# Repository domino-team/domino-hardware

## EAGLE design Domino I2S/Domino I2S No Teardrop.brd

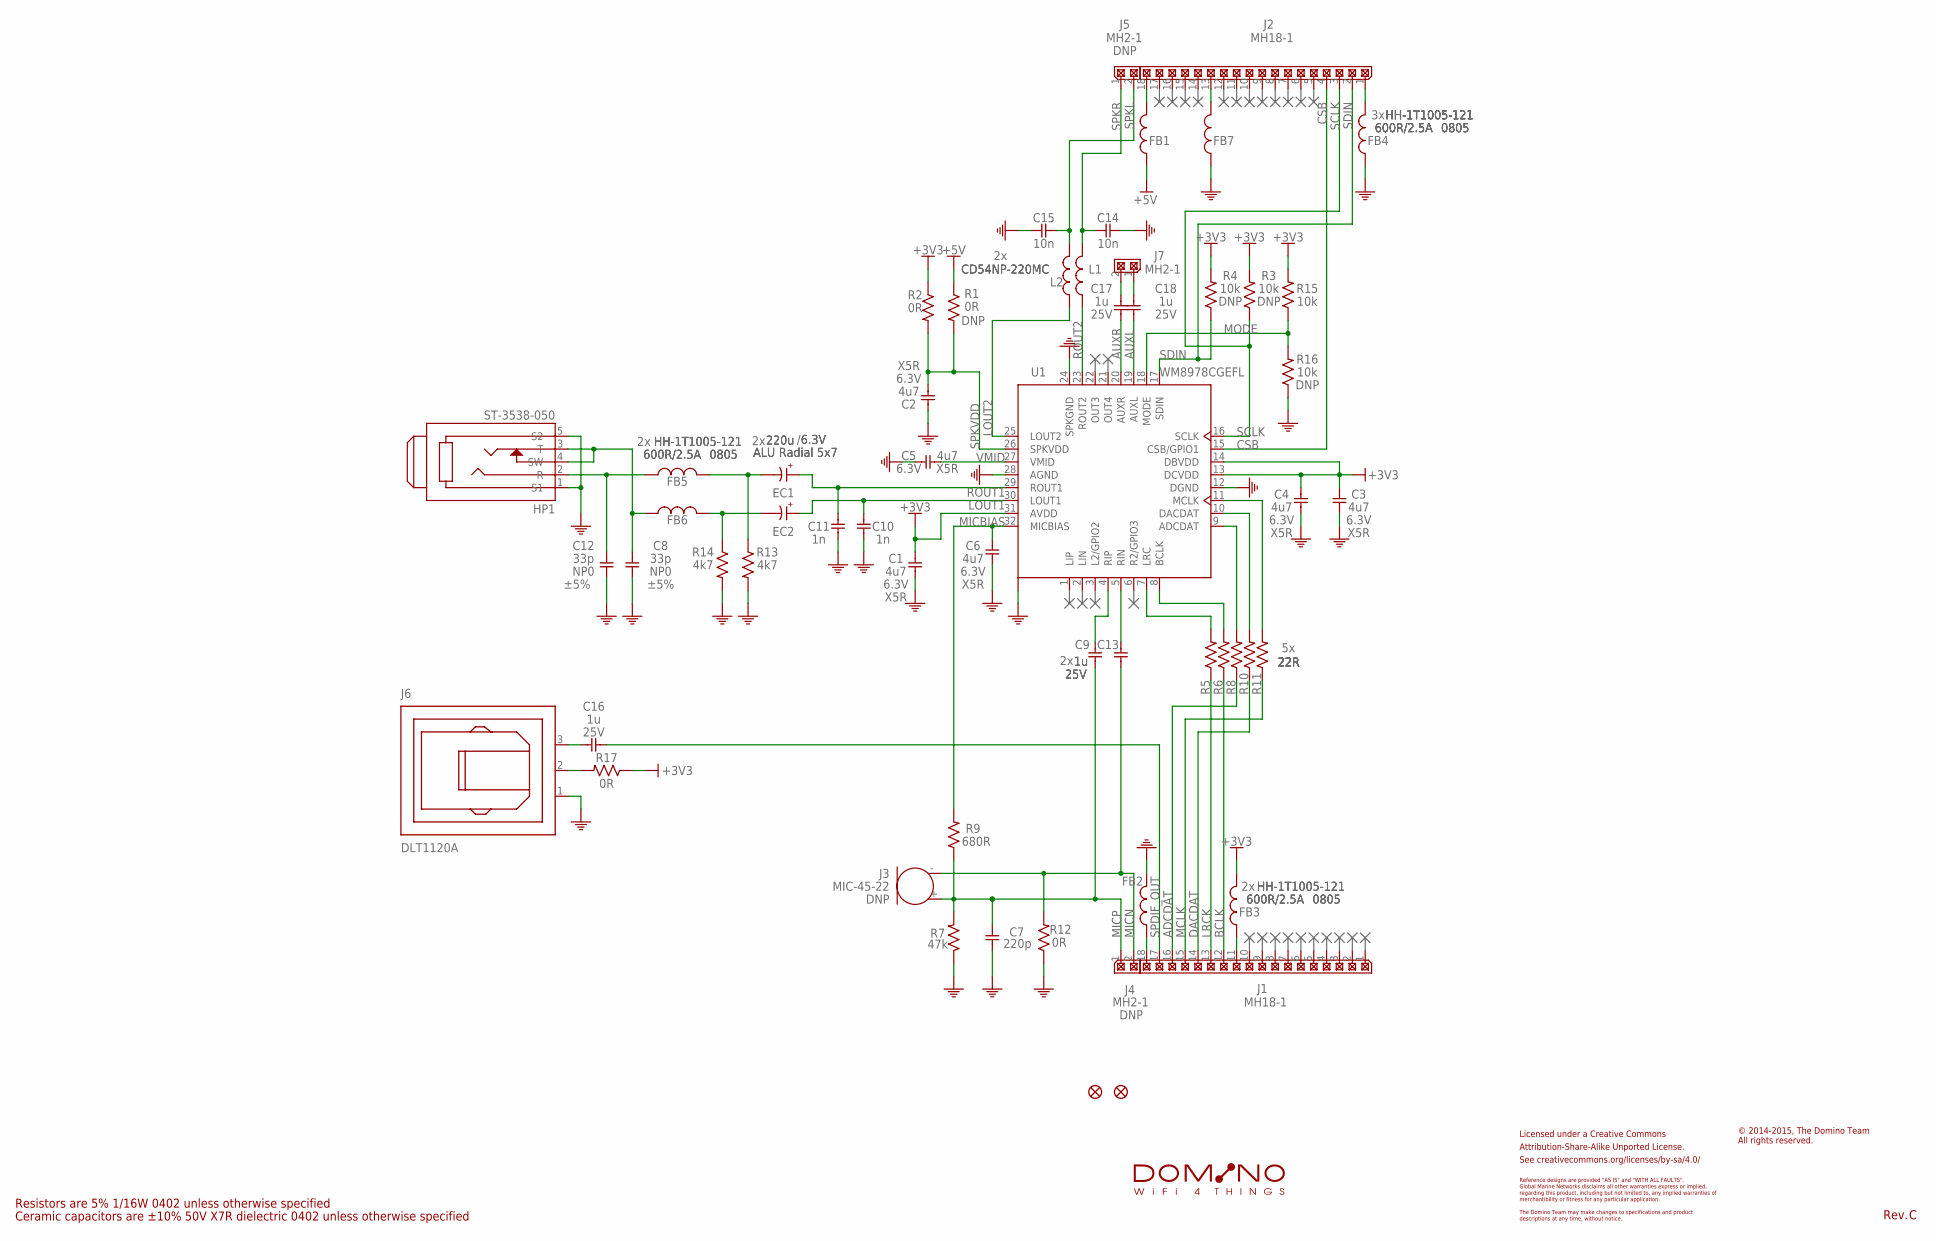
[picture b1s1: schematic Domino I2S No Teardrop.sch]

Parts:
C1, C2, C3, C4, C5, C6: 4u7; C0402; PARTNO C0402_4u7_X5R_10%_CER_6V3
C7: 220p; C0402; PARTNO C0402_220p_X7R_10%_CER_50V
C8, C12: 33p; C0402; PARTNO C0402_33p_NP0_5%_CER_50V
C9, C13, C16, C17, C18: 1u; C0402; PARTNO C0402_1u_X7R_10%_CER_25V
C10, C11: 1n; C0402; PARTNO C0402_1n_X7R_10%_CER_50V
C14, C15: 10n; C0402; PARTNO C0402_10n_X7R_10%_CER_50V
CC-BY-SA101: CC-BY-SA_LOGO
EC1, EC2: 220u; E2-5; PARTNO C2-5x7_220u_ALU_20%_RAD_6V3
F1, F2: FIDUCIAL
FB1, FB2, FB3, FB4, FB5, FB6, FB7: HH-1T1005-121; FB0805; PARTNO HH-1T2012-601
HP1: ST-3538-050; PARTNO ST-3538-050
J1, J2: MH18-1; MH18-1-0.1; PARTNO MH18-1-0.1
J3: MIC-45-22; PARTNO MIC-45-22
J4, J5, J7: MH2-1; MH2-1-0.1; PARTNO MH2-1-0.1
J6: DLT1120A; PARTNO DLT1120A
L1, L2: CD54NP-220MC; CD54; PARTNO CD54NP-220MC
R1, R2, R12, R17: 0R; R0402; PARTNO R0402_0R_5%_62.5mW
R3, R4, R15, R16: 10k; R0402; PARTNO R0402_10k_5%_62.5mW
R5, R6, R8, R10, R11: 22R; R0402; PARTNO R0402_22R_5%_62.5mW
R7: 47k; R0402; PARTNO R0402_47k_5%_62.5mW
R9: 680R; R0402; PARTNO R0402_680R_5%_62.5mW
R13, R14: 4k7; R0402; PARTNO R0402_4k7_5%_62.5mW
S101: DOMINO_LOGO
U1: WM8978CGEFL; QFN-32_EP_5X5; PARTNO WM8978CGEFL

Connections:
+3V3: C1.1, C3.1, C4.1, FB3.2, R2.1, R3.2, R4.2, R15.2, R17.1, U1.13 (DCVDD), U1.14 (DBVDD), U1.31 (AVDD)
+5V: FB1.1, R1.1
ADCDAT: J1.16, R8.1
AUXL: C18.2, U1.19 (AUXL)
AUXR: C17.2, U1.20 (AUXR)
BCLK: J1.12, R6.1
CSB: J2.4, U1.15 (CSB/GPIO1)
DACDAT: J1.14, R10.1
GND: C1.2, C2.1, C3.2, C4.2, C5.1, C6.2, C7.2, C8.1, C10.2, C11.2, C12.1, C14.2, C15.2, FB2.2, FB4.1, FB7.1, HP1.1 (S1), HP1.5 (S2), J6.1 (GND), R7.1, R12.1, R13.2, R14.2, R16.1, U1.12 (DGND), U1.24 (SPKGND), U1.28 (AGND), U1.PAD
LOUT1: C10.1, EC2.1 (+), U1.30 (LOUT1)
LOUT2: L2.1, U1.25 (LOUT2)
LRCK: J1.13, R5.1
MCLK: J1.15, R11.1
MICBIAS: C6.1, R9.2, U1.32 (MICBIAS)
MICN: C13.2, J3.-, J4.2, R12.2
MICP: C7.1, C9.2, J3.+, J4.1, R7.2, R9.1
MODE: R15.1, R16.2, U1.18 (MODE)
unnamed: R5.2, U1.7 (LRC)
unnamed: R6.2, U1.8 (BCLK)
unnamed: R8.2, U1.9 (ADCDAT)
unnamed: R10.2, U1.10 (DACDAT)
unnamed: R11.2, U1.11 (MCLK)
unnamed: C9.1, U1.4 (RIP)
unnamed: C13.1, U1.5 (RIN)
unnamed: C16.1, J6.3 (VIN)
unnamed: J6.2 (VCC), R17.2
unnamed: FB2.1, J1.18
unnamed: FB1.2, J2.18
unnamed: EC1.2 (-), FB5.2, R13.1
unnamed: EC2.2 (-), FB6.2, R14.1
unnamed: FB3.1, J1.11
unnamed: FB7.2, J2.13
unnamed: C8.2, FB6.1, HP1.3 (T), HP1.4 (SW)
unnamed: C12.2, FB5.1, HP1.2 (R)
unnamed: FB4.2, J2.1
unnamed: C17.1, J7.2
unnamed: C18.1, J7.1
ROUT1: C11.1, EC1.1 (+), U1.29 (ROUT1)
ROUT2: L1.1, U1.23 (ROUT2)
SCLK: J2.3, R3.1, U1.16 (SCLK)
SDIN: J2.2, R4.1, U1.17 (SDIN)
SPDIF_OUT: C16.2, J1.17
SPKL: C15.1, J5.2, L2.2
SPKR: C14.1, J5.1, L1.2
SPKVDD: C2.2, R1.2, R2.2, U1.26 (SPKVDD)
VMID: C5.2, U1.27 (VMID)

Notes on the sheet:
Ceramic capacitors are ±10% 50V X7R dielectric 0402 unless otherwise specified
Resistors are 5% 1/16W 0402 unless otherwise specified
Licensed under a Creative Commons
Attribution-Share-Alike Unported License.
See creativecommons.org/licenses/by-sa/4.0/
Reference designs are provided "AS IS" and "WITH ALL FAULTS".
regarding this product, including but not limited to, any implied warranties of
The Domino Team may make changes to specifications and product
Global Marine Networks disclaims all other warranties express or implied,
merchantibility or fitness for any particular application.
descriptions at any time, without notice.
© 2014-2015, The Domino Team All rights reserved.
Rev.

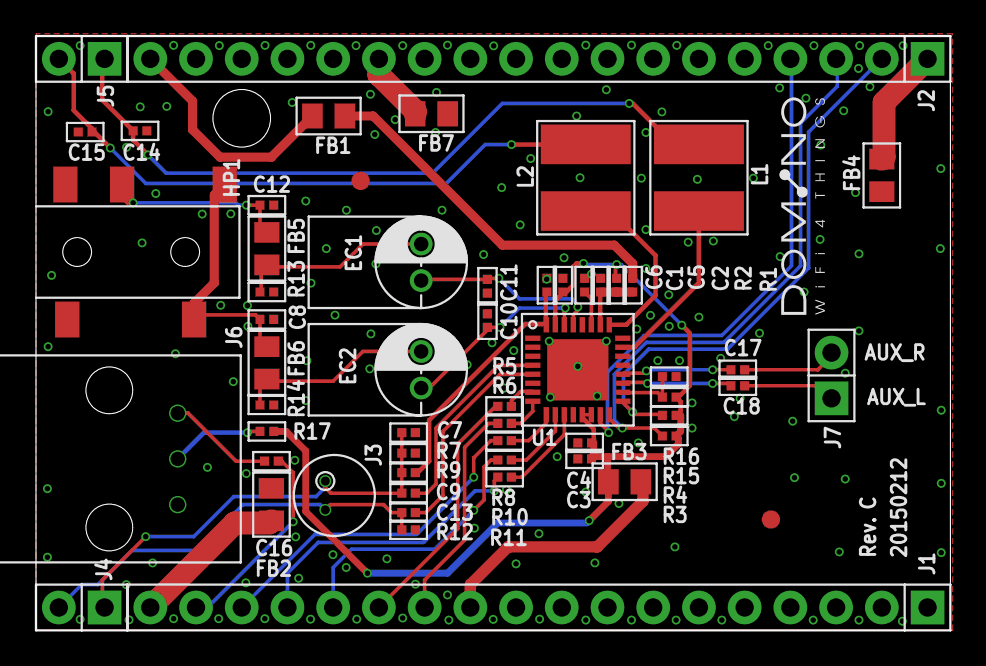
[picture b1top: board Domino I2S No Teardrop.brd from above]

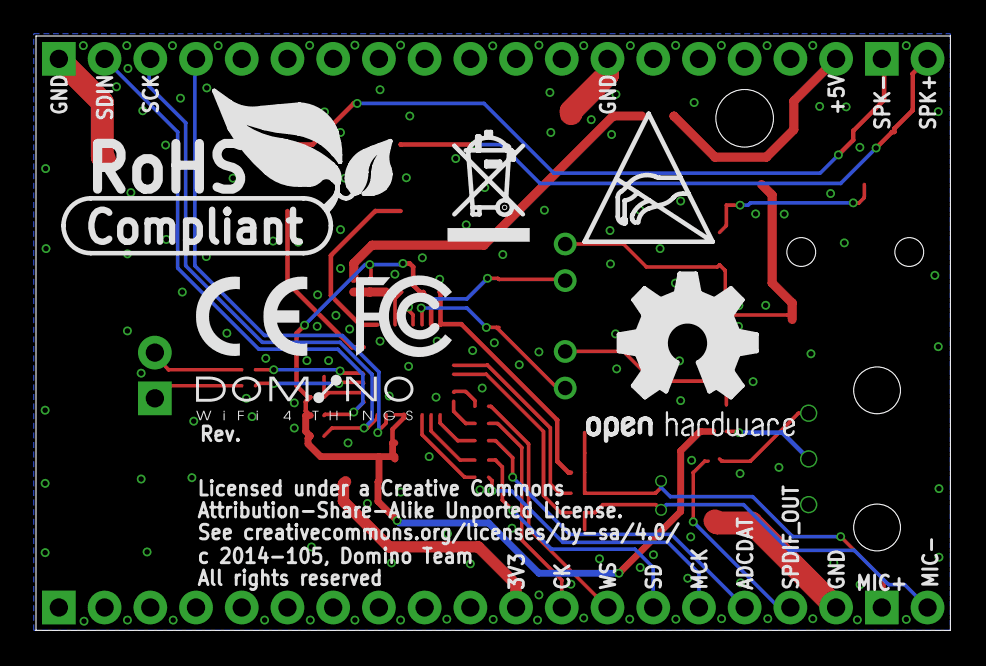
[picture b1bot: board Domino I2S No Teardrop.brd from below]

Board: 2 copper layers, 50.8 x 33.0 mm, 69 parts (7 on the bottom side), 46 nets.

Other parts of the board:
DRILEGEND: DRILEGEND
U$3: A5L-LOC
U$12, U$14: DOMINO_LOGO_SMALL
U$13: RECYCLE_BIN_LOGO
U$15: ESD_LOGO
U$16: OPEN_HARDWARE_LOGO
U$20: CE_LOGO_SMALL
U$21: FCC_LOGO_SMALL
U$22: ROHS_LOGO

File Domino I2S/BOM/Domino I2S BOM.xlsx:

Item | Qty | Value | Manufacturer | Device | Package | Reference | Description | Remarks
1 | 6 | 4u7 | ANY | C0402_4u7_X5R_10%_CER_6V3 | C0402 | C1, C2, C3, C4, C5, C6 | CAP CER 4.7UF 6.3V 10% X5R 0402
2 | 2 | 1n | ANY | C0402_1n_X7R_10%_CER_50V | C0402 | C10, C11 | CAP CER 1NF 50V 10% X7R 0402
3 | 2 | 10n | ANY | C0402_10n_X7R_10%_CER_50V | C0402 | C14, C15 | CAP CER 10000PF 50V 10% X7R 0402
4 | 1 | 220p | ANY | C0402_220p_X7R_10%_CER_50V | C0402 | C7 | CAP CER 0.22UF 50V 10% X7R 0402
5 | 2 | 33p | ANY | C0402_33p_NP0_5%_CER_50V | C0402 | C8, C12 | CAP CER 33PF 50V 5% NP0 0402
6 | 5 | 1u | ANY | C0402_1u_X7R_10%_CER_25V | C0402 | C9, C13, C16, C17, C18 | CAP CER 1UF 25V 10% X7R 0402
7 | 2 | 220u | ANY | C2-5x7_220u_ALU_20%_RAD_6V3 | E2-5 | EC1, EC2 | CAP ALUM 220UF 6.3V 20% RADIAL
8 | 7 | HH-1T1005-121 | CERATECH | HH-1T2012-601 | FB0805 | FB1, FB2, FB3, FB4, FB5, FB6, FB7 | FERRITE CHIP 600 OHM 2500MA 0805
9 | 1 | ST-3538-050 | SZJUSTWELL ELECTRONICS | ST-3538-050 | ST-3538-050 | HP1 | CONN AUDIO JACK 3.5MM STEREO SMD
10 | 2 | MH18-1 | ANY | MH18-1-0.1 | MH18-1-0.1 | J1, J2 | CONN HEADER VERT .100 1ROW 18POS 8.08 HEAD 3.05 TAIL 15AU
11 | 0 | MIC-45-22 | ANY | MIC-45-22 | MIC-45-22 | J3(DNP) | MIC COND ANALOG OMNI
12 | 1 | MH2-1 | ANY | MH2-1-0.1 | MH2-1-0.1 | J4(DNP), J5(DNP), J7 | CONN HEADER VERT .100 1ROW 2POS 8.08 HEAD 3.05 TAIL 15AU
13 | 1 | DLT1120A | AIXIN LTD | DLT1120A | DLT1120A | J6 | TRANSMITTER FIBER OPTIC 16MBPS
14 | 2 | CD54NP-220MC | SUMIDA INC | CD54NP-220MC | CD54 | L1, L2 | FIXED IND 220UH 1.11A 190 MOHM
15 | 3 | 0R | ANY | R0402_0R_5%_62.5mW | R0402 | R1(DNP), R2, R12, R17 | RES 0.0 OHM 1/16W JUMP 0402 SMD
16 | 2 | 4k7 | ANY | R0402_4k7_5%_62.5mW | R0402 | R13, R14 | RES 4.7K OHM 1/16W 5% 0402 SMD
17 | 1 | 10k | ANY | R0402_10k_5%_62.5mW | R0402 | R3(DNP), R4(DNP), R15, R16(DNP) | RES 10K OHM 1/16W 5% 0402 SMD
18 | 5 | 22R | ANY | R0402_22R_5%_62.5mW | R0402 | R5, R6, R8, R10, R11 | RES 22 OHM 1/16W 5% 0402 SMD
19 | 1 | 47k | ANY | R0402_47k_5%_62.5mW | R0402 | R7 | RES 47K OHM 1/16W 5% 0402 SMD
20 | 1 | 680R | ANY | R0402_680R_5%_62.5mW | R0402 | R9 | RES 680 OHM 1/16W 5% 0402 SMD
21 | 1 | WM8978CGEFL | CIRRUS LOGIC | WM8978CGEFL | QFN-32_EP_5X5 | U1 | IC CODEC STER SPEAKER DVR 32QF

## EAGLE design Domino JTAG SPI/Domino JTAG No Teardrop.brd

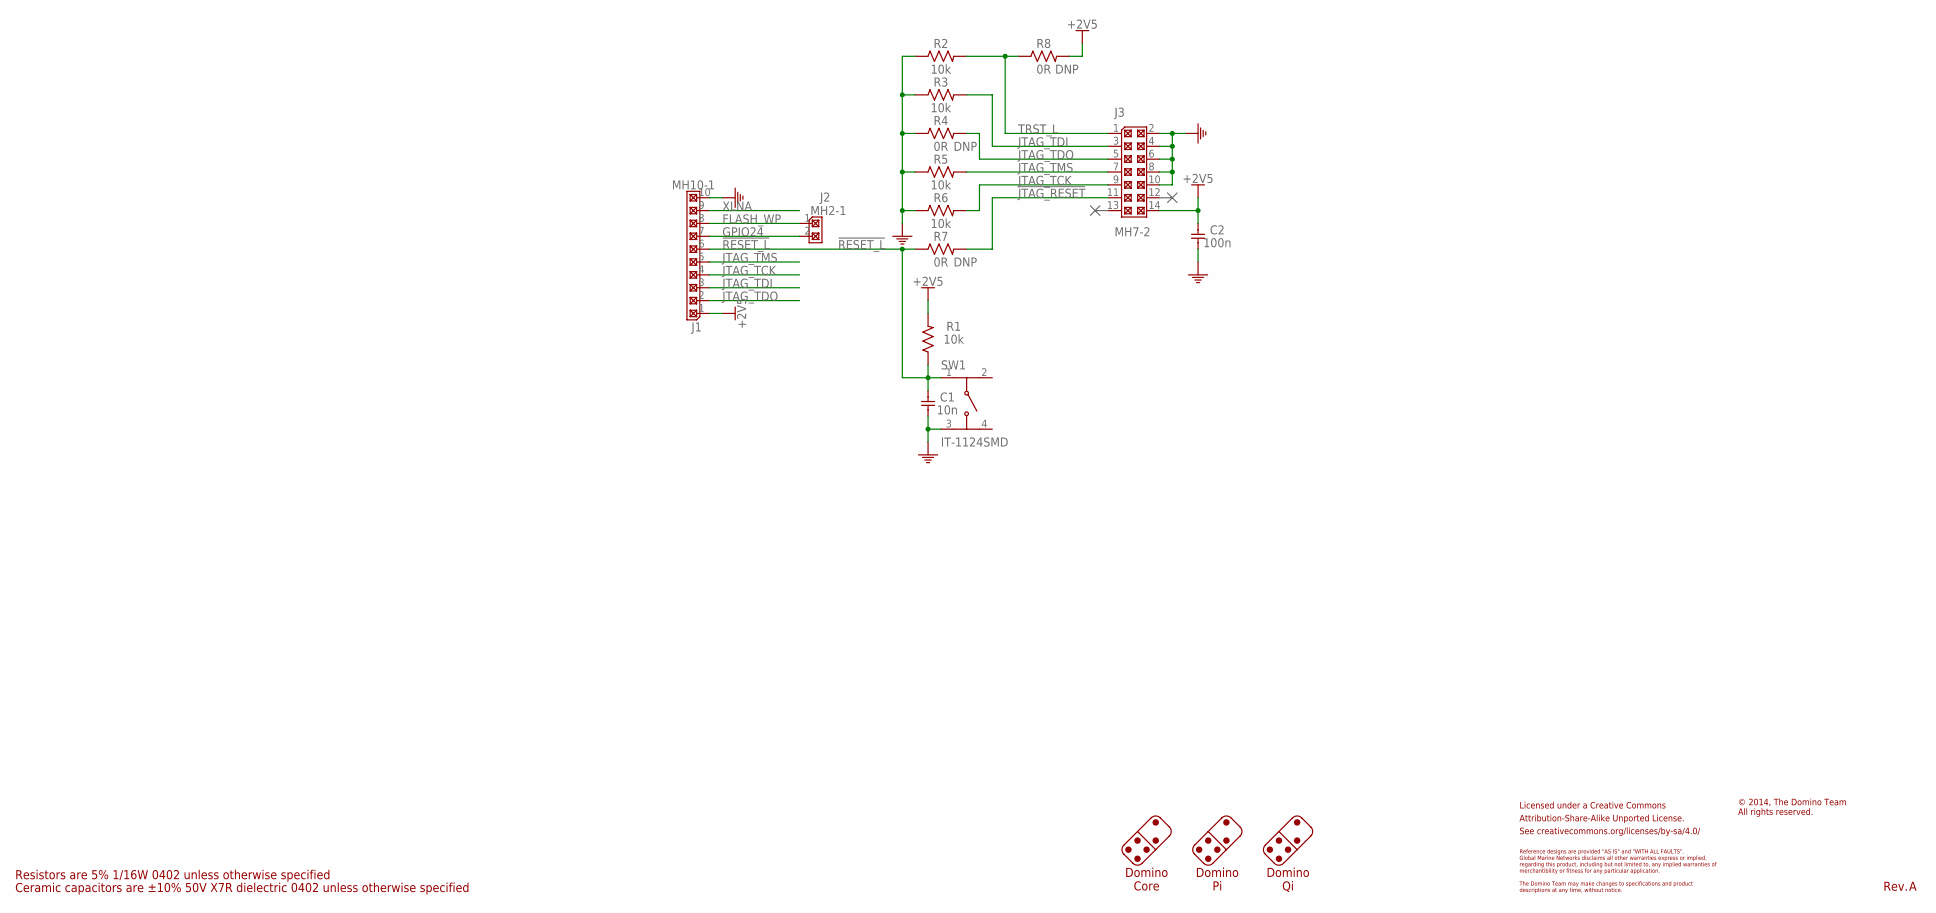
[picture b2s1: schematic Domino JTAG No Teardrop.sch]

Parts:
C1: 10n; C0402; PARTNO C0402_10n_X7R_10%_CER_50V
C2: 100n; C0402; PARTNO C0402_100n_X7R_10%_CER_50V
CC-BY-SA1: CC-BY-SA_LOGO
J1: MH10-1; MH10-1-0.1; PARTNO MH10-1-0.1
J2: MH2-1; MH2-1-0.1; PARTNO MH2-1-0.1
J3: MH7-2; MH7-2-0.1; PARTNO MH7-2-0.1
R1, R2, R3, R5, R6: 10k; R0402; PARTNO R0402_10k_5%_62.5mW
R4, R7, R8: 0R; R0603; PARTNO R0603_0R_5%_125mW
SW1: IT-1124SMD; PARTNO IT-1124SMD

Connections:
!JTAG_RESET: J3.11, R7.2
!RESET_L: C1.1, J1.6, R1.1, R7.1, SW1.1
+2V5: C2.1, J1.1, J3.14, R1.2, R8.2
FLASH_WP: J1.8, J2.1
GND: C1.2, C2.2, J1.10, J3.2, J3.4, J3.6, J3.8, J3.10, R2.1, R3.1, R4.1, R5.1, R6.1, SW1.3
GPIO24: J1.7, J2.2
JTAG_TCK: J1.4, J3.9, R6.2
JTAG_TDI: J1.3, J3.3, R3.2
JTAG_TDO: J1.2, J3.5, R4.2
JTAG_TMS: J1.5, J3.7, R5.2
TRST_L: J3.1, R2.2, R8.1
XLNA: J1.9

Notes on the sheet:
Ceramic capacitors are ±10% 50V X7R dielectric 0402 unless otherwise specified
Resistors are 5% 1/16W 0402 unless otherwise specified
Licensed under a Creative Commons
Attribution-Share-Alike Unported License.
See creativecommons.org/licenses/by-sa/4.0/
Reference designs are provided "AS IS" and "WITH ALL FAULTS".
regarding this product, including but not limited to, any implied warranties of
The Domino Team may make changes to specifications and product
Global Marine Networks disclaims all other warranties express or implied,
merchantibility or fitness for any particular application.
descriptions at any time, without notice.
Domino Core
Domino Pi
Domino Qi
© 2014, The Domino Team All rights reserved.
Rev.

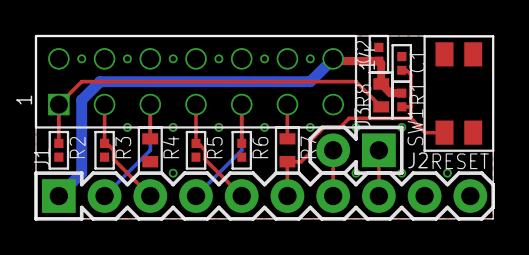
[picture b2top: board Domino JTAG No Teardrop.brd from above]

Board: 2 copper layers, 25.4 x 10.2 mm, 18 parts (1 on the bottom side), 11 nets.

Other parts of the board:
DRILEGEND: DRILEGEND
U$3: A5L-LOC
U$4: DOMINO_LOGO_SMALL

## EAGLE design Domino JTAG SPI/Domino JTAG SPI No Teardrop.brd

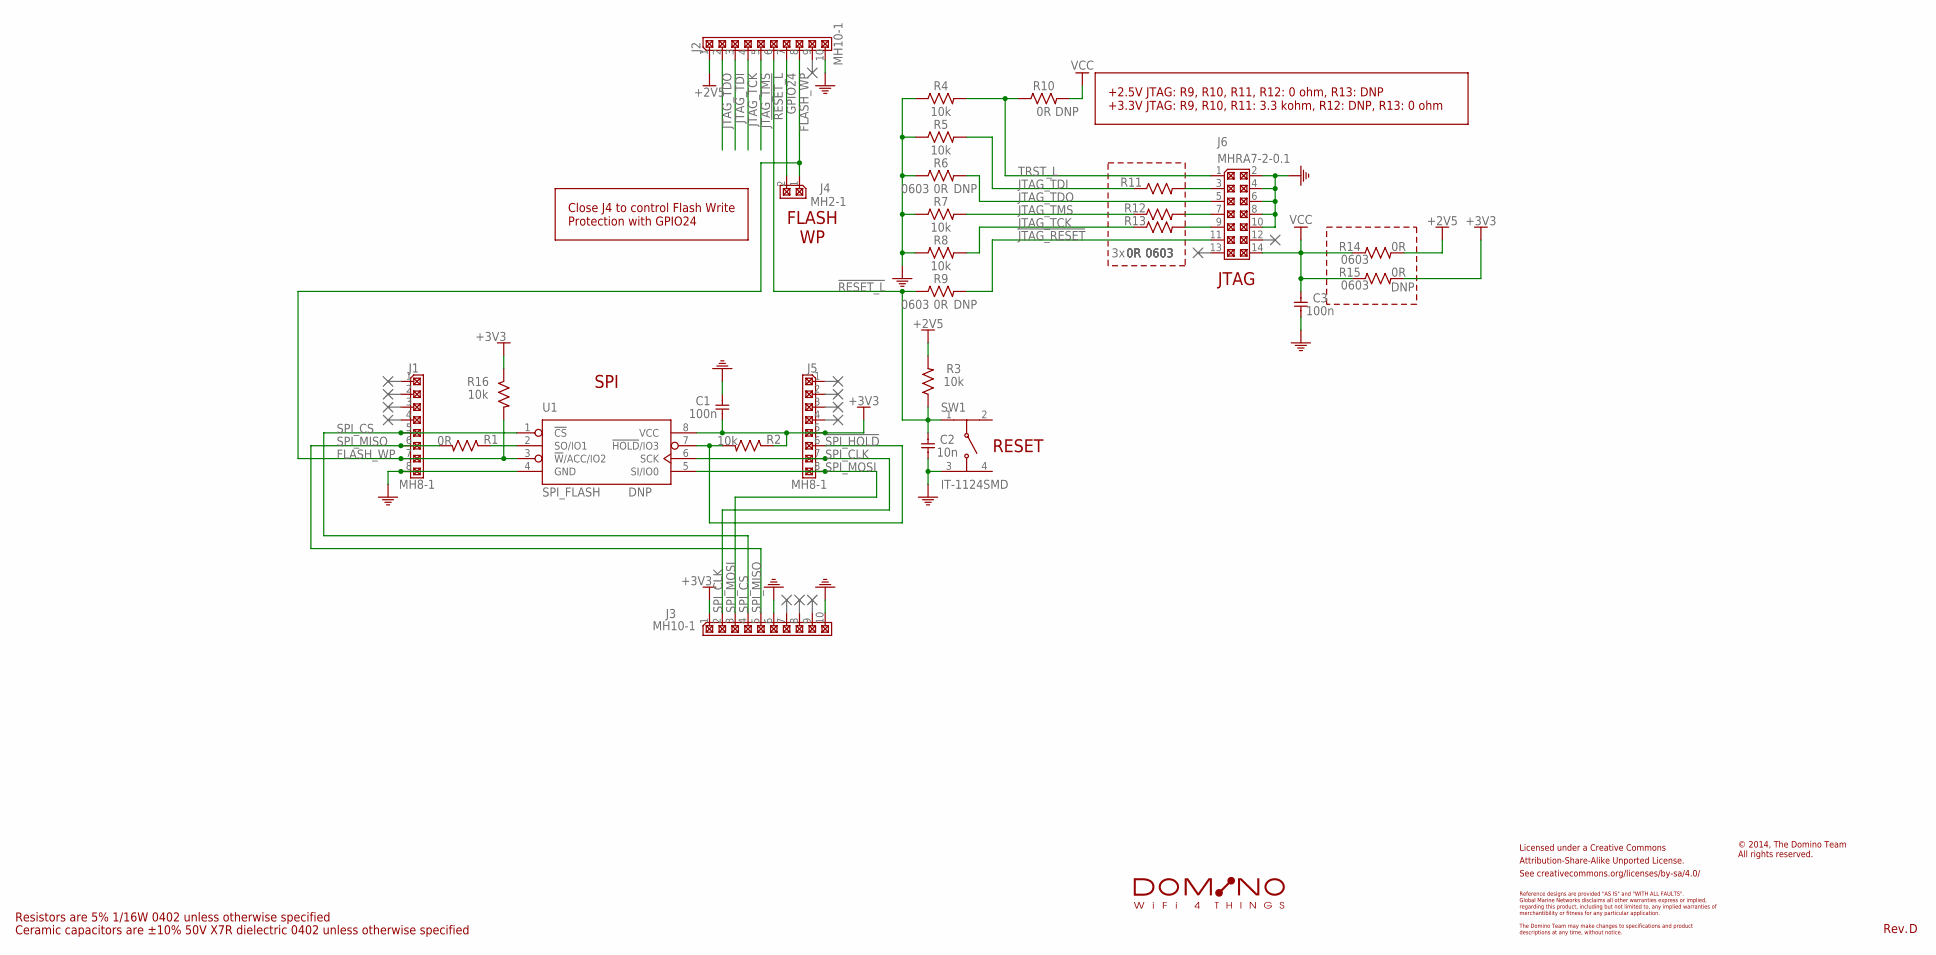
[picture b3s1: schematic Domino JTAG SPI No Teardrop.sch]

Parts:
C1, C3: 100n; C0402; PARTNO C0402_100n_X7R_10%_CER_50V
C2: 10n; C0402; PARTNO C0402_10n_X7R_10%_CER_50V
CC-BY-SA1: CC-BY-SA_LOGO
J1, J5: MH8-1; MH8-1-0.1; PARTNO MH8-1-0.1
J2, J3: MH10-1; MH10-1-0.1; PARTNO MH10-1-0.1
J4: MH2-1; MH2-1-0.1; PARTNO MH2-1-0.1
J6: MHRA7-2-0.1; PARTNO MHRA7-2-0.1
R1: 0R; R0402; PARTNO R0402_0R_5%_62.5mW
R2, R3, R4, R5, R7, R8, R16: 10k; R0402; PARTNO R0402_10k_5%_62.5mW
R6, R9, R10, R11, R12, R13, R14, R15: 0R; R0603; PARTNO R0603_0R_5%_125mW
SW1: IT-1124SMD; PARTNO IT-1124SMD
U1: SPI_FLASH; SOIC-8; PARTNO SPI_FLASH
U$2: DOMINO_LOGO

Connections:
!JTAG_RESET: J6.11, R9.2
!RESET_L: C2.1, J2.6, R3.1, R9.1, SW1.1
!SPI_HOLD: J5.6, R2.2, U1.7 (!HOLD!/IO3)
+2V5: J2.1, R3.2, R14.2
+3V3: C1.2, J3.1, J5.5, R2.1, R15.2, R16.1, U1.8 (VCC)
FLASH_WP: J1.7, J2.8, J4.1, R16.2, U1.3 (!W!/ACC/IO2)
GND: C1.1, C2.2, C3.2, J1.8, J2.10, J3.6, J3.10, J6.2, J6.4, J6.6, J6.8, J6.10, R4.1, R5.1, R6.1, R7.1, R8.1, SW1.3, U1.4 (GND)
GPIO24: J2.7, J4.2
JTAG_TCK: J2.4, R8.2, R13.1
JTAG_TDI: J2.3, R5.2, R11.1
JTAG_TDO: J2.2, J6.5, R6.2
JTAG_TMS: J2.5, R7.2, R12.1
unnamed: J6.7, R12.2
unnamed: J6.9, R13.2
unnamed: J6.3, R11.2
unnamed: R1.1, U1.2 (SO/IO1)
SPI_CLK: J3.2, J5.7, U1.6 (SCK)
SPI_CS: J1.5, J3.4, U1.1 (!CS)
SPI_MISO: J1.6, J3.5, R1.2
SPI_MOSI: J3.3, J5.8, U1.5 (SI/IO0)
TRST_L: J6.1, R4.2, R10.1
VCC: C3.1, J6.14, R10.2, R14.1, R15.1

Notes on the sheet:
Ceramic capacitors are ±10% 50V X7R dielectric 0402 unless otherwise specified
Resistors are 5% 1/16W 0402 unless otherwise specified
Licensed under a Creative Commons
Attribution-Share-Alike Unported License.
See creativecommons.org/licenses/by-sa/4.0/
Reference designs are provided "AS IS" and "WITH ALL FAULTS".
regarding this product, including but not limited to, any implied warranties of
The Domino Team may make changes to specifications and product
Global Marine Networks disclaims all other warranties express or implied,
merchantibility or fitness for any particular application.
descriptions at any time, without notice.
© 2014, The Domino Team All rights reserved.
Rev.
FLASH WP
SPI
JTAG
+2.5V JTAG: R9, R10, R11, R12: 0 ohm, R13: DNP +3.3V JTAG: R9, R10, R11: 3.3 kohm, R12: DNP, R13: 0 ohm
Close J4 to control Flash Write Protection with GPIO24
RESET

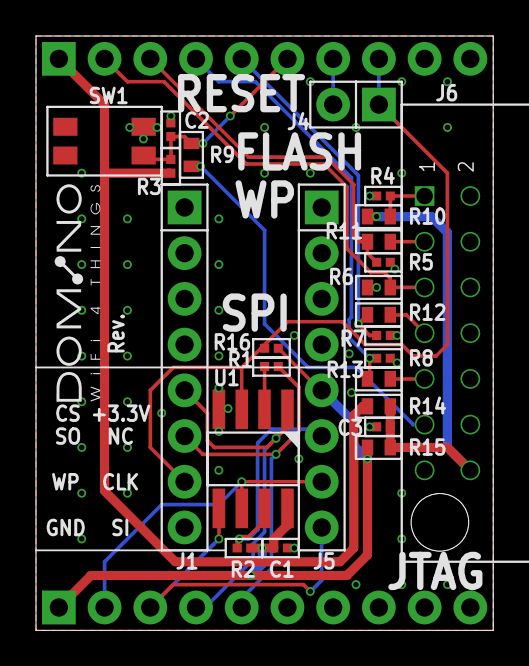
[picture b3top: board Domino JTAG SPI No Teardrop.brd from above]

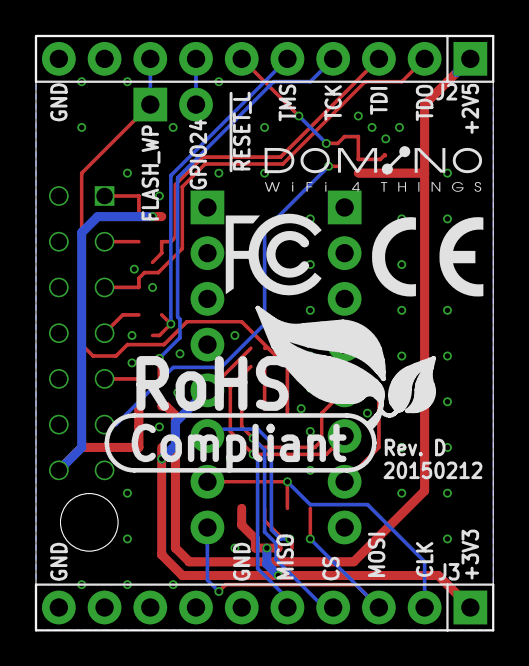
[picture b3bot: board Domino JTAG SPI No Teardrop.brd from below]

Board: 2 copper layers, 25.4 x 33.0 mm, 36 parts (6 on the bottom side), 22 nets.

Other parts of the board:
DRILEGEND: DRILEGEND
U$3: A5L-LOC
U$6: ROHS_LOGO
U$8: CE_LOGO_SMALL
U$10: FCC_LOGO_SMALL
U$11, U$12: DOMINO_LOGO_SMALL

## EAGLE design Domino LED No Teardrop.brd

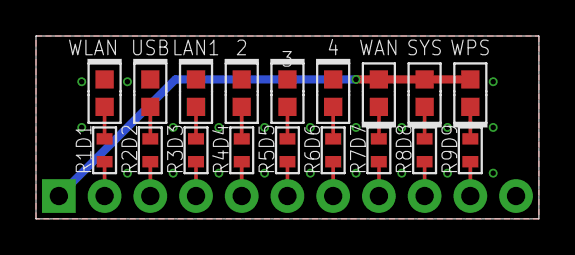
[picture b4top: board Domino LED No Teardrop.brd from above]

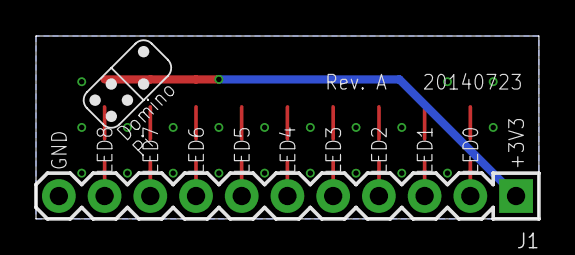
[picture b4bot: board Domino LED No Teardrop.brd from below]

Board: 2 copper layers, 27.9 x 10.2 mm, 23 parts (2 on the bottom side), 20 nets.

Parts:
CC-BY-SA1: CC-BY-SA_LOGO
D1: BLUE; LED0603
D2: WHITE; LED0603
D3, D4, D5, D6: GREEN; LED0603
D7: RED; LED0603
D8: ORANGE; LED0603
D9: YELLOW; LED0603
DRILEGEND: DRILEGEND
J1: MH11-1; MH11-1-0.1
R1, R2, R3, R4, R5, R6: 270R; R0603
R7, R8, R9: 330R; R0603
U$3: A5L-LOC
U$4: DOMINO_LOGO_SMALL

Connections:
+3V3: D7.2, D8.2, D9.2, J1.1
GND: D1.1, D2.1, D3.1, D4.1, D5.1, D6.1, J1.11
LED0: J1.2, R1.1
LED1: J1.3, R2.1
LED2: J1.4, R3.1
LED3: J1.5, R4.1
LED4: J1.6, R5.1
LED5: J1.7, R6.1
LED6: J1.8, R7.1
LED7: J1.9, R8.1
LED8: J1.10, R9.1
unnamed: D1.2, R1.2
unnamed: D2.2, R2.2
unnamed: D3.2, R3.2
unnamed: D4.2, R4.2
unnamed: D5.2, R5.2
unnamed: D7.1, R7.2
unnamed: D8.1, R8.2
unnamed: D9.1, R9.2
unnamed: D6.2, R6.2

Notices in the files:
Domino LED No Teardrop.brd:
© 2014, Michel Stempin.
All rights reserved.
parts and their libraries:
Domino: See creativecommons.org/licenses/by-sa/4.0/ for details.
Domino: See creativecommons.org/licenses/by-sa/3.0/ for details.
Domino: Copyright © 2012, Michel Stempin, All rights reserved
Licenced under Creative Commons CC BY-SA 3.0 license.
